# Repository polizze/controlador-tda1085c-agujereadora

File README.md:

# Controlador de Velocidad a Lazo Cerrado (`TDA1085C`) para Agujereadora de Banco — Acople Directo

Proyecto de **Hardware Libre** para el diseño electrónico, simulación SPICE (**LTspice**) y diseño de circuito impreso (**KiCad**) de un controlador de velocidad a lazo cerrado proporcional-integral (PI) por ángulo de fase basado en el circuito integrado **`TDA1085C`**, destinado a adaptar un motor universal de lavarropas (**Askoll / C.E.SET. `MCA 52/64-148/ALL7`**) en una **agujereadora de banco de acople directo** (regulando entre **$400\text{ RPM}$ y $2.500\text{ RPM}$** con alto torque a bajas vueltas).

---

> [!CAUTION]
> ### ⚠️ ADVERTENCIA DE SEGURIDAD ELÉCTRICA VITAL: TRIAC `BTB12-600BW` (ALETA NO AISLADA) Y CHASIS VIVO
> 1. **Aleta Metálica Viva ($220\text{ V AC}$):** Este diseño reutiliza un Triac **`BTB12-600BW`**. A diferencia de la serie `BTA` (aislada internamente), la sigla **`BTB`** indica que **la aleta metálica del encapsulado TO-220 está conectada internamente de forma directa al terminal `MT2` (`A2`)**. En consecuencia, **todo el disipador de aluminio extruido ($4 \times 2 \times 8\text{ cm}$) se encuentra permanentemente electrificado a potencial de red de $220\text{ V AC}$**.
> 2. **Prohibición de Contacto con el Chasis:** El disipador **JAMÁS debe tocar el chasis metálico** de la agujereadora de banco ni ningún elemento accesible al operador. Debe montarse rígidamente soportado sobre el PCB dentro de un gabinete plástico aislante cerrado, o bien aislar el TO-220 mediante **lámina de Mica/Kapton + grasa térmica siliconada + niple pasamuros aislante (bushing plástico) en el tornillo M3**, verificando aislación ($> 20\text{ M}\Omega$) con multímetro antes de conectar a la red.
> 3. **Masa de Control Sin Aislación Galvánica (`GND_CHIP`):** El circuito integrado `TDA1085C` opera referenciado directamente al polo `L1` (Neutro) de la línea de $220\text{ V AC}$. El eje del potenciómetro de panel debe ser plástico o contar con perilla aislante, y cualquier medición con osciloscopio requiere transformador de aislación o sondas diferenciales.
> 4. **Puesta a Tierra Obligatoria (`PE`):** El bastidor metálico de la agujereadora y la carcasa del motor deben conectarse obligatoriamente al conductor de **Tierra de Protección (`PE` Verde/Amarillo)** de la instalación eléctrica bajo interruptor diferencial ($30\text{ mA}$).

---

## 1. Estructura del Repositorio

```text
.
├── Docs/                                   # Documentación técnica, relevamiento fotográfico y cálculos
│   ├── Calculos_y_Notas_Diseno.md          # Memoria de cálculo actualizada (Pinout real, R=8.6Ω, Tacho=73Ω, Lazo PI)
│   ├── TDA1085C-D.PDF                      # Hoja de datos oficial ON Semiconductor TDA1085C
│   ├── BTA12.PDF                           # Hoja de datos oficial STMicroelectronics BTA12 / BTB12-600BW
│   ├── conector.jpg                        # Relevamiento de bornera de 7 pines del motor C.E.SET.
│   ├── filtro emi.jpg                      # Filtro EMI pasivo de entrada FLCR47050 (16A)
│   ├── placadearriba.jpg                   # Vista superior placa donante E.G.O.
│   └── placadeabajo.jpg                    # Vista inferior placa donante E.G.O.
├── Hardware/                               # Diseño de esquemático, PCB y fabricación en KiCad 10
│   ├── TDA1085C_Controller/
│   │   ├── TDA1085C_Controller.kicad_pro   # Proyecto KiCad con Netclasses (HV_AC clearance 3.0mm)
│   │   ├── TDA1085C_Controller.kicad_sch   # Esquemático completo del controlador TDA1085C (Rev 2.1)
│   │   ├── TDA1085C_Controller.kicad_pcb   # Layout PCB (Star Ground en MT1 + barrera > 3.0mm)
│   │   ├── TDA1085C_Controller.kicad_dru   # Reglas DRC personalizadas de alta tensión y potencia
│   │   ├── fp-lib-table                    # Tabla de librería de huellas locales del proyecto
│   │   └── TDA1085C_Custom.pretty/         # Footprints dedicados (R 3W elevada pad 2.5/1.2mm y BTB12+Disipador)
│   ├── Fabrication/                        # Vistas previas exportadas listas para revisión/impresión
│   │   ├── Esquematico_TDA1085C.pdf        # Esquemático en PDF
│   │   ├── TDA1085C_Controller.svg         # Esquemático vectorial SVG
│   │   ├── PCB_TDA1085C_Preview.pdf        # Layout PCB en PDF
│   │   └── PCB_TDA1085C_Preview.svg        # Layout PCB vectorial SVG
│   └── BOM_KiCad.csv                       # Lista de materiales exportada desde KiCad + parámetros medidos
├── Simulations/                            # Simulaciones SPICE verificadas en LTspice 26.1
│   ├── etapa2_lazo_pi_conversor_fv.asc          # Modelo dinámico del Conversor F-V (Tacho 73Ω) y Lazo PI (Pin 16)
│   ├── etapa2_lazo_pi_conversor_fv.net          # Netlist SPICE del Conversor F-V y Lazo PI
│   ├── etapa2_lazo_pi_conversor_fv.log          # Mediciones del transitorio bajo carga del Lazo PI
│   ├── tda1085c_controlador_completo_btb12.asc  # Esquemático maestro completo (Estator 2.1Ω + Rotor 6.5Ω + BTB12)
│   ├── tda1085c_controlador_completo_btb12.net  # Netlist SPICE ejecutable del modelo completo
│   ├── tda1085c_controlador_completo_btb12.log  # Resultados medidos (.meas) del modelo maestro
│   ├── etapa1a_fuente_tda1085c.asc              # Análisis de fuente sin transformador y estrés de carga
│   ├── etapa1b_conversor_fv_tacho.asc           # Análisis del conversor F/V (400 RPM vs 2.500 RPM)
│   └── etapa1c_triac_snubber_motor.asc          # Análisis de conmutación inductiva, Snubber y dV/dt
├── .gitignore                              # Reglas de exclusión estándar para KiCad y LTspice
├── init_repo.sh                            # Script Bash de inicialización y estructuración Git
└── README.md                               # Documentación principal del proyecto
```

---

## 2. Parámetros Físicos Medidos y Pinout Definitivo del Motor

### A. Motor Universal (`Askoll / C.E.SET. MCA 52/64-148/ALL7`)
* **Datos nominales de placa:** $220\text{–}240\text{ V AC}$, $50\text{ Hz}$ | $1.5\text{ A}$ | $330\text{ W}$ (entrada) | $11.000\text{ RPM}$.
* **Rango de Operación en Agujereadora (Acople Directo):** **$400\text{ RPM}$ a $2.500\text{ RPM}$** para el $100\%$ del giro del potenciómetro de panel.
* **Parámetros de Potencia Medidos en Banco:**
  * **Resistencia del Estator (Campo):** $R_{\text{estator}} = \mathbf{2.1\text{ }\Omega}$ *(medida entre **Pin 1** y **Pin 5**)*.
  * **Resistencia del Rotor (Inducido / Armadura):** $R_{\text{rotor}} = \mathbf{6.5\text{ }\Omega}$ *(medida entre **Pin 2** y **Pin 6**)*.
  * **Resistencia Total en Serie (DC):** $R_{\text{total}} = R_{\text{estator}} + R_{\text{rotor}} = \mathbf{8.6\text{ }\Omega}$.
  * **Inductancia Total en Serie Estimada:** $L_{\text{total}} \approx \mathbf{25\text{ mH}\text{ a }30\text{ mH}}$ ($28\text{ mH}$ en simulación: $15\text{ mH}$ campo + $13\text{ mH}$ inducido).
* **Parámetros del Generador Tacométrico Medidos (Pines 3 y 4):**
  * **Polos Magnéticos:** **$8\text{ polos}$** ($4$ pares de polos $\rightarrow 4$ ciclos AC por revolución).
  * **Resistencia de la Bobina:** $R_{\text{tacho}} = \mathbf{73.0\text{ }\Omega}$.
  * **Frecuencia a $2.500\text{ RPM}$ (Tope deseado):** $f_{\text{max}} = \mathbf{166.6\text{ Hz}}$ ($f_{\text{min}} = 26.67\text{ Hz}$ a $400\text{ RPM}$).

### B. Pinout Definitivo de la Bornera de 7 Pines (de Izquierda a Derecha)

Se utiliza el mazo de cables inferior original que vincula los pines **1, 2, 5 y 6** para establecer la conexión en serie:

| Pin Bornera (Izq. $\rightarrow$ Der.) | Color de Cable | Bobinado / Elemento Interno | Conexión en el Controlador (`MOTOR_OUT` / `TACHO`) |
| :---: | :--- | :--- | :--- |
| **Pin 1** | **Gris oscuro** | **Estator (Campo A)** | **Puente Serie:** Unir directamente con **Pin 2 (Violeta)** |
| **Pin 2** | **Violeta** | **Rotor (Carbón Izquierdo)** | **Puente Serie:** Unir directamente con **Pin 1 (Gris oscuro)** |
| **Pin 3** | **Rojo fino** | **Generador Tacométrico ($73.0\text{ }\Omega$)** | Entrada `TACHO_AC` en Bornera `J3` Pin 1 ($\rightarrow R_{12} = 10\text{ k}\Omega$) |
| **Pin 4** | **Rojo fino** | **Generador Tacométrico ($73.0\text{ }\Omega$)** | Masa `GND_CHIP` en Bornera `J3` Pin 2 |
| **Pin 5** | **Negro** | **Estator (Campo B)** | **Alimentación (`MOTOR_OUT`):** Conectar a Bornera `J1` Pin 3 (`L2_AC_HOT`) |
| **Pin 6** | **Azul** | **Rotor (Carbón Derecho)** | **Alimentación (`MOTOR_OUT`):** Conectar a Bornera `J1` Pin 2 (`MT2` del Triac `BTB12-600BW`) |
| **Pin 7** | **Gris claro** | **Estator (Tap o Térmico interno)** | **Sin uso** en esta configuración (dejar aislado) |

### C. Diagrama de Conexión en Serie y Bloques del Controlador

```mermaid
flowchart LR
    subgraph RED["Red 220V AC 50Hz + Filtro EMI FLCR47050"]
        L2["Fase (L2_AC_HOT)"]
        L1["Neutro (L1)"]
        PE["Tierra (PE)"]
    end

    subgraph PCB["PCB Controlador TDA1085C (Hardware/)"]
        STAR(("Pad MT1\n(Star Ground)"))
        Q1["Triac BTB12-600BW\n(I_GT = 50mA | Aleta Viva en MT2)\n+ Disipador 40x20x80mm Aislado"]
        SNUB["Snubber RC\n100Ω 1W + 100nF X2"]
        PSU["Fuente Sin Transformador\n1N4007 + 2x 4.7kΩ 3W (Elevadas 5mm)\n+ C_VCC1 = 220µF/25V"]
        U1["IC TDA1085C\nPin 8 = GND_CHIP (única pista desde MT1)\nPin 13 -> R_GATE1 150Ω 1W\nPin 12 <- R12 10kΩ + C12 10nF\nPin 16 -> Red PI (47kΩ + 1µF || 47nF)"]
        POT["Consigna 400-2500 RPM\nPin 9 (+VCC) -> Preset 50kΩ Multivuelta (RV1)\n-> Pot. Panel 10kΩ (Pin 5) -> R_MIN1 2.2kΩ"]
    end

    subgraph MOTOR["Motor Universal C.E.SET. MCA 52/64 (R_tot = 8.6Ω, L = 25-30mH)"]
        EST["Estator (Campo: 2.1Ω)\nPin 5 (Negro) a Pin 1 (Gris oscuro)"]
        PUENTE["PUENTE SERIE\nPin 1 (Gris oscuro) === Pin 2 (Violeta)"]
        ROT["Rotor (Armadura: 6.5Ω)\nPin 2 (Violeta) a Pin 6 (Azul)"]
        TACHO["Pines 3 y 4 (Rojos)\nTacómetro AC: 73.0Ω | 8 Polos\n166.6 Hz @ 2.500 RPM"]
        CHASIS["Carcasa Metálica Motor + Agujereadora\n(Pin 7 Gris claro: Aislado sin uso)"]
    end

    PE --> CHASIS
    L1 -- "Pista gruesa 3.0mm (J1 Pin 1)" --> STAR
    STAR -- "MT1" --> Q1
    STAR -- "ÚNICA pista Star Ground" --> U1
    L2 -- "J1 Pin 3 (L2_MOT_PIN5)" --> EST
    L2 -- "J1 Pin 4" --> PSU
    PSU -- "+15.24V (Pin 9/10)" --> U1
    POT -- "Pin 5 (V_SET)" --> U1
    U1 -- "Pulso 88mA pk (R_G=150Ω 1W)" --> Q1
    EST --> PUENTE --> ROT
    Q1 -- "J1 Pin 2 (MT2 -> Pin 6 Azul)" --> ROT
    Q1 --- SNUB --- STAR
    TACHO -- "J3 (Pines 3 y 4)" --> U1
```

### D. Relevamiento Fotográfico del Hardware
| Motor y Bornera (`Docs/conector.jpg`) | Filtro EMI (`Docs/filtro emi.jpg`) | Placa Superior (`Docs/placadearriba.jpg`) | Placa Inferior (`Docs/placadeabajo.jpg`) |
| :---: | :---: | :---: | :---: |
|  |  |  |  |

---

## 3. Simulaciones SPICE Actualizadas (`LTspice 26.1.1`)

| Esquemático (`.asc`) | Netlist (`.net`) | Resultados (`.log`) | Descripción |
| :--- | :--- | :--- | :--- |
| [`etapa2_lazo_pi_conversor_fv.asc`](Simulations/etapa2_lazo_pi_conversor_fv.asc) | [`etapa2_lazo_pi_conversor_fv.net`](Simulations/etapa2_lazo_pi_conversor_fv.net) | [`etapa2_lazo_pi_conversor_fv.log`](Simulations/etapa2_lazo_pi_conversor_fv.log) | **Conversor F/V y Lazo PI (Pines 12, 11, 4, 5 y 16):** Tacómetro real ($R_{\text{tacho}}=73.0\text{ }\Omega$, $8$ polos, $166.6\text{ Hz}$ a $2.500\text{ RPM}$), filtro $10\text{ k}\Omega + 10\text{ nF}$, bomba de carga $C_{11}=1\text{ nF}$, integrador $R_4=270\text{ k}\Omega \parallel 470\text{ nF}$ y respuesta dinámica del compensador PI ($47\text{ k}\Omega + 1\text{ }\mu\text{F} \parallel 47\text{ nF}$) ante escalón de carga de perforación. |
| [`tda1085c_controlador_completo_btb12.asc`](Simulations/tda1085c_controlador_completo_btb12.asc) | [`tda1085c_controlador_completo_btb12.net`](Simulations/tda1085c_controlador_completo_btb12.net) | [`tda1085c_controlador_completo_btb12.log`](Simulations/tda1085c_controlador_completo_btb12.log) | **Modelo Maestro Completo:** Fuente sin transformador ($2\times 4.7\text{ k}\Omega\text{ 3W} + 220\text{ }\mu\text{F}$), disparo de Gate ($150\text{ }\Omega\text{ 1W}$, $87.9\text{ mA pk}$), motor serie con Estator ($2.1\text{ }\Omega + 15\text{ mH}$) + Puente Pin 1–Pin 2 + Rotor ($6.5\text{ }\Omega + 13\text{ mH} + \text{FEM}$) y Triac `BTB12-600BW`. |
| [`etapa1a_fuente_tda1085c.asc`](Simulations/etapa1a_fuente_tda1085c.asc) | [`etapa1a_fuente_tda1085c.net`](Simulations/etapa1a_fuente_tda1085c.net) | [`etapa1a_fuente_tda1085c.log`](Simulations/etapa1a_fuente_tda1085c.log) | Evaluación térmica y de rizado de la fuente sin transformador. |
| [`etapa1b_conversor_fv_tacho.asc`](Simulations/etapa1b_conversor_fv_tacho.asc) | [`etapa1b_conversor_fv_tacho.net`](Simulations/etapa1b_conversor_fv_tacho.net) | [`etapa1b_conversor_fv_tacho.log`](Simulations/etapa1b_conversor_fv_tacho.log) | Comparativa del conversor F/V a $400\text{ RPM}$ ($26.67\text{ Hz}$) y $2.500\text{ RPM}$ ($166.6\text{ Hz}$) con $R_{\text{tacho}} = 73.0\text{ }\Omega$. |
| [`etapa1c_triac_snubber_motor.asc`](Simulations/etapa1c_triac_snubber_motor.asc) | [`etapa1c_triac_snubber_motor.net`](Simulations/etapa1c_triac_snubber_motor.net) | [`etapa1c_triac_snubber_motor.log`](Simulations/etapa1c_triac_snubber_motor.log) | Conmutación inductiva con $R_{\text{tot}} = 8.6\text{ }\Omega$ y $L_{\text{tot}} = 28\text{ mH}$. |

---

## 4. Reglas Críticas de Diseño PCB (DRC) en KiCad

1. **Clearance de Alta Tensión ($> 3.0\text{ mm}$):** Separación física $> 3.5\text{ mm}$ entre las pistas `HV_AC` (`L2_AC_HOT`, `MT2`) y toda la sección lógica referenciada a `GND_CHIP`.
2. **Topología de Masa en Estrella (*Star Ground*):** La pista gruesa de `L1` ($220\text{ V}$) entra al pad `MT1` del Triac `Q1`. Desde ese pad sale **UNA ÚNICA pista** hacia el Pin 8 del `TDA1085C`, evitando bucles de corriente de armadura bajo el integrado.
3. **Manejo Térmico en PCB:** Las dos resistencias de caída ($4.7\text{ k}\Omega\text{ 3 W}$) cuentan con pads de **$2.5\text{ mm}$ (agujero $1.2\text{ mm}$)** en [`R_Axial_3W_Elevated_Pad2.5mm_Drill1.2mm.kicad_mod`](Hardware/TDA1085C_Controller/TDA1085C_Custom.pretty/R_Axial_3W_Elevated_Pad2.5mm_Drill1.2mm.kicad_mod) para ser montadas a **$5\text{ mm}$ de altura sobre el PCB**.
4. **Protección del Tacómetro:** Huella para el capacitor cerámico `C12` ($10\text{ nF}$) en paralelo con la entrada del Pin 12 (después de `R12` = $10\text{ k}\Omega$) para absorber picos inductivos.

---

## 5. Lista de Materiales Definitiva (BOM)

Sincronizada con [`Hardware/BOM_KiCad.csv`](Hardware/BOM_KiCad.csv):

| Referencia | Cant. | Valor / Especificación | Función en el Circuito | Footprint KiCad | Notas de Montaje / Parámetros |
| :--- | :---: | :--- | :--- | :--- | :--- |
| **`U1`** | 1 | **`TDA1085C`** | Controlador de velocidad a lazo cerrado PI | `Package_DIP:DIP-16_W7.62mm_Socket_LongPads` | Montar sobre zócalo DIP-16 |
| **`Q1`** | 1 | **`BTB12-600BW`** | Triac $12\text{ A }600\text{ V}$ Snubberless ($I_{GT}=50\text{ mA}$) | `TDA1085C_Custom:BTB12-600BW_Heatsink_40x20x80mm_LIVE_TAB` | **¡ALETA VIVA EN MT2! Aislar del chasis** |
| **`D1`** | 1 | **`1N4007`** | Rectificador de media onda ($1000\text{ V }1\text{ A}$) | `Diode_THT:D_DO-41_SOD81_P10.16mm_Horizontal` | Fuente sin transformador |
| **`R_DROP1, R_DROP2`** | 2 | **$4.7\text{ k}\Omega\text{ / 3 W}$** | Caída de tensión AC a $+V_{CC}$ ($9.4\text{ k}\Omega$ serie) | `TDA1085C_Custom:R_Axial_3W_Elevated_Pad2.5mm_Drill1.2mm` | MOX. **Montar a $5\text{ mm}$ sobre el PCB** |
| **`R_GATE1`** | 1 | **$150\text{ }\Omega\text{ / 1 W}$** | Limitadora de pulso de Gate ($88\text{ mA pk}$) | `Resistor_THT:R_Axial_DIN0411_L9.9mm_D3.6mm_P12.70mm_Horizontal` | Garantiza disparo para $I_{GT}=50\text{ mA}$ |
| **`R_SNUB1`** | 1 | **$100\text{ }\Omega\text{ / 1 W}$** | Amortiguación red Snubber RC (`MT1-MT2`) | `Resistor_THT:R_Axial_DIN0411_L9.9mm_D3.6mm_P12.70mm_Horizontal` | Protección ante chispazo de escobillas |
| **`C_SNUB1`** | 1 | **$100\text{ nF / 400 V X2}$** | Capacitor de seguridad red Snubber RC | `Capacitor_THT:C_Rect_L18.0mm_W6.0mm_P15.00mm_FKS3_FKP3` | Polipropileno Clase X2 ($275\text{ Vac}$) |
| **`C_VCC1`** | 1 | **$220\text{ }\mu\text{F / 25 V}$** | Filtro electrolítico principal de $+V_{CC}$ (Pin 9/10) | `Capacitor_THT:CP_Radial_D10.0mm_P5.00mm` | Compatible con $220\text{ }\mu\text{F}$ o $470\text{ }\mu\text{F / 25 V}$ |
| **`C_DEC1, C3, C5`** | 3 | **$100\text{ nF / 50 V}$** | Desacoplo $+V_{CC}$, filtro `I_LIM` (Pin 3) y `V_SET` (Pin 5) | `Capacitor_THT:C_Disc_D5.0mm_W2.5mm_P5.00mm` | Cerámico X7R |
| **`C12`** | 1 | **$10\text{ nF / 50 V}$** | Protección contra picos inductivos en Tacómetro (Pin 12) | `Capacitor_THT:C_Disc_D5.0mm_W2.5mm_P5.00mm` | En paralelo tras `R12` a `GND_CHIP` |
| **`C11`** | 1 | **$1\text{ nF}$** (o $470\text{ pF}$) | Bomba de carga conversor F/V (Pin 11, $166.6\text{ Hz}$ max) | `Capacitor_THT:C_Rect_L7.2mm_W3.5mm_P5.00mm_FKS2_FKP2_MKS2_MKP2` | Film polipropileno (FKP2/MKP2) o NP0 |
| **`C4`** | 1 | **$470\text{ nF / 63 V}$** | Integrador de velocidad real en Pin 4 ($5.14\text{ V} @ 2.500\text{ RPM}$) | `Capacitor_THT:C_Rect_L7.2mm_W3.5mm_P5.00mm_FKS2_FKP2_MKS2_MKP2` | Poliéster metalizado (MKS2) |
| **`C7`** | 1 | **$4.7\text{ }\mu\text{F / 50 V}$** | Rampa de arranque suave (*Soft-Start*, Pin 7) | `Capacitor_THT:CP_Radial_D6.3mm_P2.50mm` | Electrolítico radial |
| **`C14`** | 1 | **$47\text{ nF / 63 V}$** | Generador diente de sierra $100\text{ Hz}$ (Pin 14) | `Capacitor_THT:C_Rect_L7.2mm_W3.5mm_P5.00mm_FKS2_FKP2_MKS2_MKP2` | Poliéster metalizado (MKS2) |
| **`C16`** | 1 | **$1\text{ }\mu\text{F / 50 V}$** | Compensación integral del lazo PI (Pin 16, $\tau_i = 47\text{ ms}$) | `Capacitor_THT:CP_Radial_D6.3mm_P2.50mm` | En serie con `R16` ($47\text{ k}\Omega$) |
| **`C17`** | 1 | **$47\text{ nF / 50 V}$** | Polo de alta frecuencia del lazo PI (Pin 16, $f_p = 72\text{ Hz}$) | `Capacitor_THT:C_Disc_D5.0mm_W2.5mm_P5.00mm` | En paralelo entre Pin 16 y `GND_CHIP` |
| **`RV1`** | 1 | **Preset $50\text{ k}\Omega$ Multivuelta** | Calibración fina del tope de $2.500\text{ RPM}$ ($\approx 24.1\text{ k}\Omega$) | `Potentiometer_THT:Potentiometer_Bourns_3296W_Vertical` | En serie con potenciómetro de panel |
| **`RV_PANEL`** | 1 | **Pot. $10\text{ k}\Omega$ Lineal (B)** | Regulación manual de velocidad ($400\text{–}2.500\text{ RPM}$) | Conectado a `J2` (`PinHeader_1x03_P2.54mm_Vertical`) | Montaje en panel con perilla aislada |
| **`R_MIN1`** | 1 | **$2.2\text{ k}\Omega\text{ / 1/4 W}$** | Piso de consigna ($400\text{ RPM}$ al $0\%$ del potenciómetro) | `Resistor_THT:R_Axial_DIN0207_L6.3mm_D2.5mm_P10.16mm_Horizontal` | Evita $V_{\text{Pin 5}} < 80\text{ mV}$ |
| **`R1, R2`** | 2 | **$820\text{ k}\Omega\text{ / 1/2 W}$** | Sincronismo de corriente (`MT2` $\rightarrow$ Pin 1) y tensión (`L2` $\rightarrow$ Pin 2) | `Resistor_THT:R_Axial_DIN0411_L9.9mm_D3.6mm_P12.70mm_Horizontal` | Alta tensión ($> 350\text{ V}$) |
| **`R3, R12`** | 2 | **$10\text{ k}\Omega\text{ / 1/4 W}$** | Referencia Pin 3 (`I_LIM`) y limitadora de Tacómetro (Pin 12) | `Resistor_THT:R_Axial_DIN0207_L6.3mm_D2.5mm_P10.16mm_Horizontal` | Metal film $1\%$ |
| **`R4, R15`** | 2 | **$270\text{ k}\Omega\text{ / 1/4 W}$** | Ganancia F/V en Pin 4 y corriente de rampa en Pin 15 | `Resistor_THT:R_Axial_DIN0207_L6.3mm_D2.5mm_P10.16mm_Horizontal` | Metal film $1\%$ |
| **`R11`** | 1 | **$470\text{ k}\Omega\text{ / 1/4 W}$** | Polarización bomba de carga Pin 11 hacia $+V_{CC}$ | `Resistor_THT:R_Axial_DIN0207_L6.3mm_D2.5mm_P10.16mm_Horizontal` | Metal film $1\%$ |
| **`R16`** | 1 | **$47\text{ k}\Omega\text{ / 1/4 W}$** | Ganancia proporcional del compensador PI (Pin 16, $K_p=16$) | `Resistor_THT:R_Axial_DIN0207_L6.3mm_D2.5mm_P10.16mm_Horizontal` | Metal film $1\%$ |
| **`J1`** | 1 | **Bornera 4P ($5.08\text{ mm}$)** | `1:L1_MT1`, `2:MT2_MOT_PIN6(Azul)`, `3:L2_MOT_PIN5(Negro)`, `4:L2_AC_HOT` | `TerminalBlock_Phoenix:TerminalBlock_Phoenix_MKDS-3-4-5.08_1x04_P5.08mm_Horizontal` | $\ge 15\text{ A} / 300\text{ V}$ |
| **`J3`** | 1 | **Bornera 2P ($5.08\text{ mm}$)** | Entrada Tacómetro **Pines 3 y 4 Rojos** ($73.0\text{ }\Omega$, $8$ polos) | `TerminalBlock_Phoenix:TerminalBlock_Phoenix_MKDS-1,5-2-5.08_1x02_P5.08mm_Horizontal` | Paso $5.08\text{ mm}$ |
| **`J2`** | 1 | **Header 3P ($2.54\text{ mm}$)** | Conector a potenciómetro de panel de $10\text{ k}\Omega$ | `Connector_PinHeader_2.54mm:PinHeader_1x03_P2.54mm_Vertical` | Paso $2.54\text{ mm}$ |
| **`M1` (Ext.)** | 1 | **Motor `C.E.SET. MCA 52/64`** | $R_{\text{est(P1-P5)}}=2.1\text{ }\Omega$, $R_{\text{rot(P2-P6)}}=6.5\text{ }\Omega$, $R_{\text{tot}}=8.6\text{ }\Omega$, $L=25\text{–}30\text{ mH}$ | Bornera de 7 Pines (Puente Pin 1 Gris osc. con Pin 2 Violeta) | Tacómetro $73.0\text{ }\Omega$, $8$ polos ($166.6\text{ Hz} @ 2.500\text{ RPM}$) |

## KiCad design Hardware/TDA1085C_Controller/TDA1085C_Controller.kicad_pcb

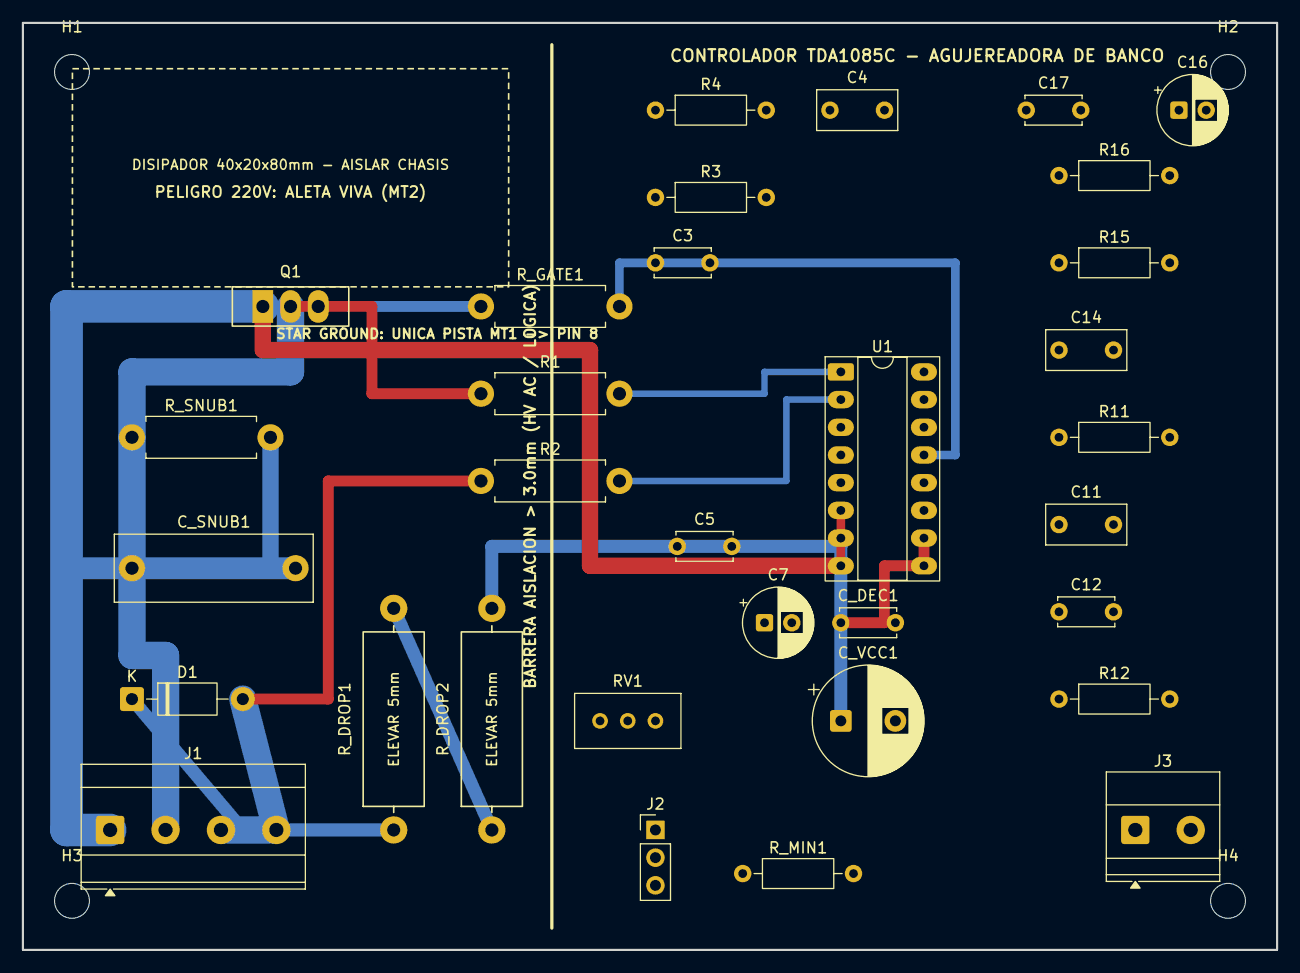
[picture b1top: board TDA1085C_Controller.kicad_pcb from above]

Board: 2 copper layers, 115.0 x 85.0 mm, 36 parts (0 on the bottom side), 24 nets.

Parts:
C3, C5: 100nF; C_Disc_D5.0mm_W2.5mm_P5.00mm
C4: 470nF; C_Rect_L7.2mm_W3.5mm_P5.00mm_FKS2_FKP2_MKS2_MKP2
C7: 4.7uF/50V; CP_Radial_D6.3mm_P2.50mm
C11: 470pF-1nF; C_Rect_L7.2mm_W3.5mm_P5.00mm_FKS2_FKP2_MKS2_MKP2
C12: 10nF; C_Disc_D5.0mm_W2.5mm_P5.00mm
C14: 47nF; C_Rect_L7.2mm_W3.5mm_P5.00mm_FKS2_FKP2_MKS2_MKP2
C16: 1uF/50V; CP_Radial_D6.3mm_P2.50mm
C17: 47nF; C_Disc_D5.0mm_W2.5mm_P5.00mm
C_DEC1: 100nF; C_Disc_D5.0mm_W2.5mm_P5.00mm
C_SNUB1: 100nF 400V X2; C_Rect_L18.0mm_W6.0mm_P15.00mm_FKS3_FKP3
C_VCC1: 220uF/25V; CP_Radial_D10.0mm_P5.00mm
D1: 1N4007; D_DO-41_SOD81_P10.16mm_Horizontal
H1, H2, H3, H4: M3_Hole; MountingHole_3.2mm_M3
J1: AC_220V_MOTOR; TerminalBlock_Phoenix_MKDS-3-4-5.08_1x04_P5.08mm_Horizontal
J2: POT_10k; PinHeader_1x03_P2.54mm_Vertical
J3: TACHO_IN; TerminalBlock_Phoenix_MKDS-1,5-2-5.08_1x02_P5.08mm_Horizont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
Q1: BTB12-600BW; BTB12-600BW_Heatsink_40x20x80mm_LIVE_TAB
R1, R2: 820k 1/2W; R_Axial_DIN0411_L9.9mm_D3.6mm_P12.70mm_Horizontal
R3, R12: 10k; R_Axial_DIN0207_L6.3mm_D2.5mm_P10.16mm_Horizontal
R4, R15: 270k; R_Axial_DIN0207_L6.3mm_D2.5mm_P10.16mm_Horizontal
R11: 470k; R_Axial_DIN0207_L6.3mm_D2.5mm_P10.16mm_Horizontal
R16: 47k; R_Axial_DIN0207_L6.3mm_D2.5mm_P10.16mm_Horizontal
RV1: 50k_Multivuelta; Potentiometer_Bourns_3296W_Vertical
R_DROP1, R_DROP2: 4.7k 3W; R_Axial_3W_Elevated_Pad2.5mm_Drill1.2mm
R_GATE1: 150R 1W; R_Axial_DIN0411_L9.9mm_D3.6mm_P12.70mm_Horizontal
R_MIN1: 2.2k; R_Axial_DIN0207_L6.3mm_D2.5mm_P10.16mm_Horizontal
R_SNUB1: 100R 1W; R_Axial_DIN0411_L9.9mm_D3.6mm_P12.70mm_Horizontal
U1: TDA1085C; DIP-16_W7.62mm_Socket_LongPads

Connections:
GATE: Q1.3, R_GATE1.1
GND_CHIP: C3.2, C4.2, C5.2, C7.2, C11.2, C12.2, C14.2, C16.2, C17.2, C_DEC1.2, C_SNUB1.2, C_VCC1.2, J1.1, J3.2, Q1.1, R3.2, R4.2, R_MIN1.2, U1.6, U1.8
L2_AC_HOT: D1.2, J1.3, J1.4, R2.1
MT2: J1.2, Q1.2, R1.1, R_SNUB1.1
N_COMP_INT: C16.1, R16.2
N_DROP_MID: R_DROP1.2, R_DROP2.1
N_POT_BOT: J2.3, R_MIN1.1
N_POT_TOP: J2.1, RV1.2, RV1.3
N_RECT: D1.1, R_DROP1.1
N_SNUB: C_SNUB1.1, R_SNUB1.2
PIN1_ISYNC: R1.2, U1.1
PIN2_VSYNC: R2.2, U1.2
PIN3_ILIM: C3.1, R3.1, U1.3
PIN4_VTACHO: C4.1, R4.1, U1.4
PIN5_VSET: C5.1, J2.2, U1.5
PIN7_RAMP: C7.1, U1.7
PIN11_PUMP: C11.1, R11.2, U1.11
PIN12_TACHO: C12.1, R12.2, U1.12
PIN13_TRIG: R_GATE1.2, U1.13
PIN14_SAW: C14.1, U1.14
PIN15_ISAW: R15.2, U1.15
PIN16_COMP: C17.1, R16.1, U1.16
TACHO_AC: J3.1, R12.1
VCC: C_DEC1.1, C_VCC1.1, R11.1, R15.1, RV1.1, R_DROP2.2, U1.9, U1.10
